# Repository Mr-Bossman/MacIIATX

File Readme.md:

# MacIIATX

## Mac II to ATX PSU adapter.

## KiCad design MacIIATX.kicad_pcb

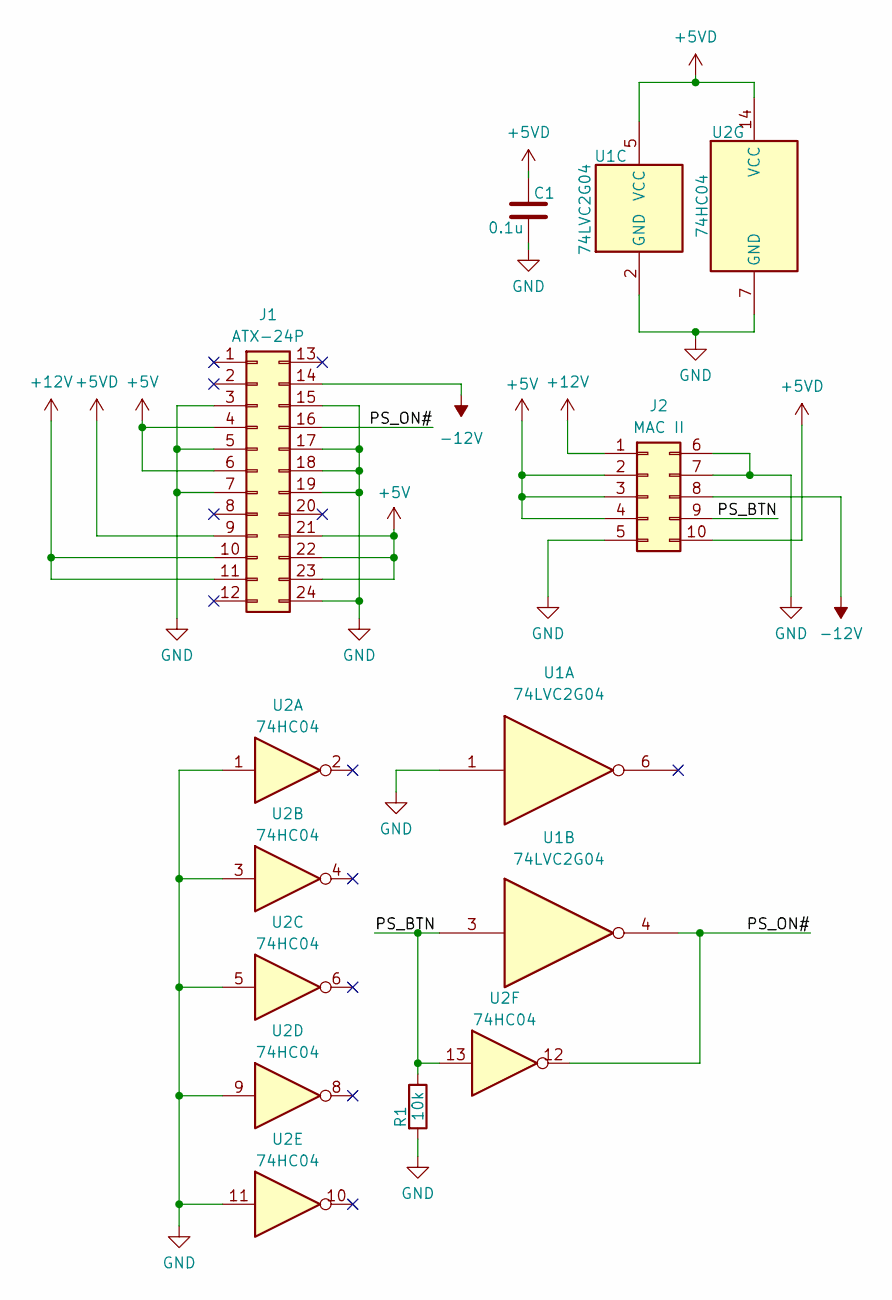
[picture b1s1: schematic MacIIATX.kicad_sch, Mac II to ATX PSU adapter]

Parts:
C1: 0.1u; C_0603_1608Metric_Pad1.08x0.95mm_HandSolder
J1: ATX-24P; Molex_Mini-Fit_Jr_5566-24A2_2x12_P4.20mm_Vertical
J2: MAC II; MacPSU_conn
R1: 10k; R_0603_1608Metric_Pad0.98x0.95mm_HandSolder
U1: 74LVC2G04; SOT-23-6
U2: 74HC04; SOIC-14_3.9x8.7mm_P1.27mm

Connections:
+5V: J1.4, J1.6, J1.21, J1.22, J1.23, J2.2, J2.3, J2.4
+5VD: C1.1, J1.9, J2.10, U1.5 (VCC), U2.14 (VCC)
+12V: J1.10, J1.11, J2.1
-12V: J1.14, J2.8
/PS_BTN: J2.9, R1.1, U1.3, U2.13
/PS_ON#: J1.16, U1.4, U2.12
GND: C1.2, J1.3, J1.5, J1.7, J1.15, J1.17, J1.18, J1.19, J1.24, J2.5, J2.6, J2.7, R1.2, U1.1, U1.2 (GND), U2.1, U2.3, U2.5, U2.7 (GND), U2.9, U2.11

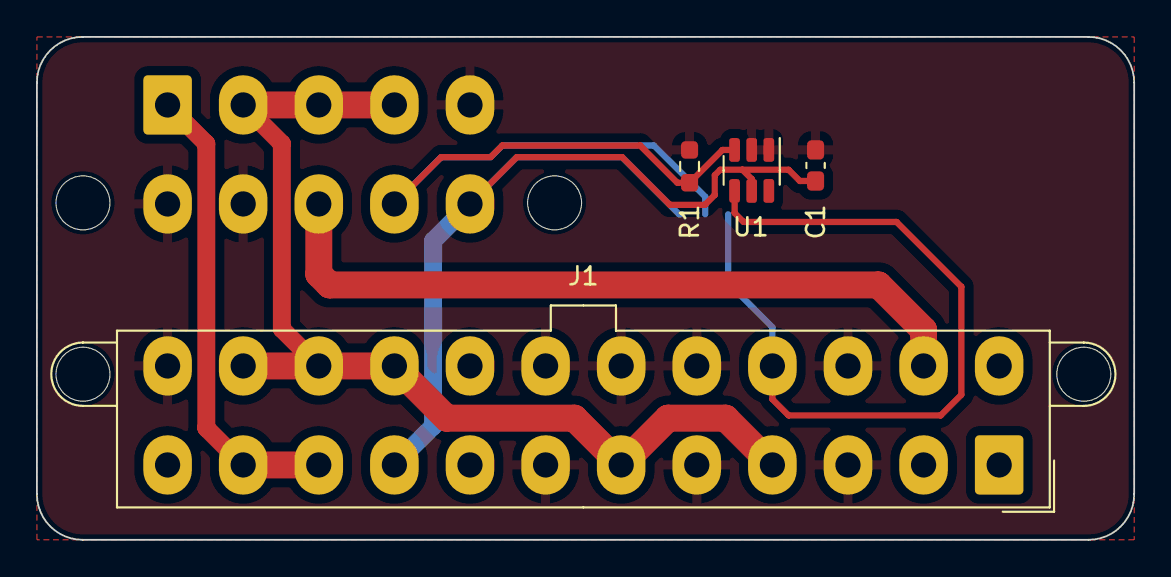
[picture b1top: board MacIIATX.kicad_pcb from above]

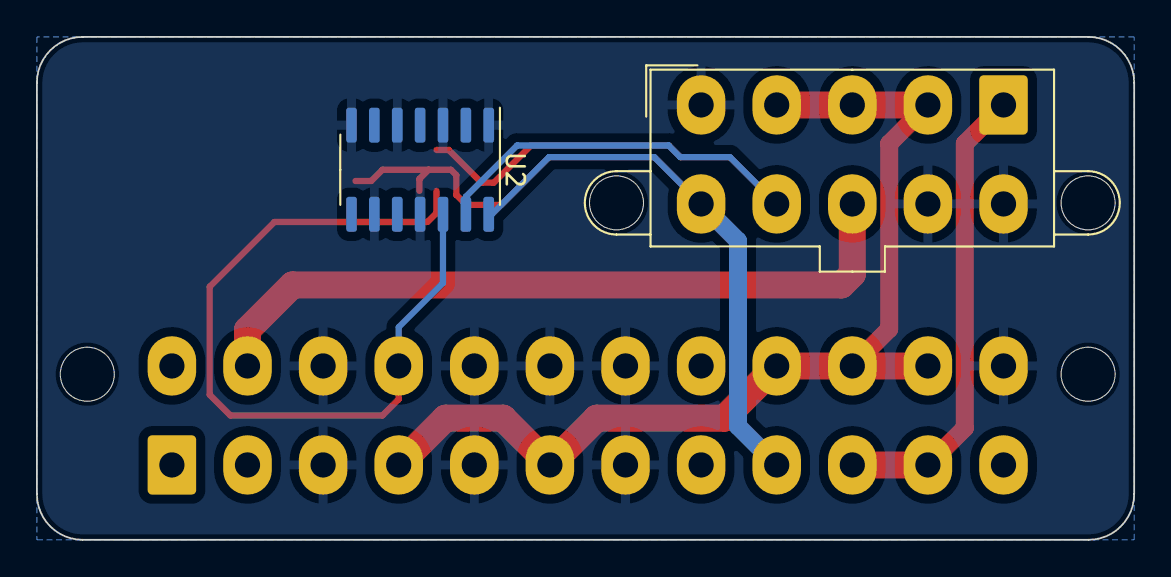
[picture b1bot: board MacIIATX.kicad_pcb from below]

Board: 2 copper layers, 61.0 x 27.9 mm, 6 parts (2 on the bottom side), 7 nets.

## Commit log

2023-11-15 init
2023-11-15 Add images and export gerber
2023-12-24 Add images
